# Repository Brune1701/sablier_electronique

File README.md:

# sablier_electronique

## Présentation

J'ai choisi de construire un minuteur, sablier, qui lance un compte à rebours de 60 sec. 
Le système s'actualise et recommence lorsqu'il est tourné, tel un sablier mécanique.

## Fonctionnement et Composants : 

- Détection de l'orientation avec le LIS3DH
- Microcontrôleur ATmega328P-AU
- 12 LEDs  pour représenter le sable qui s'écoule
- Compte à rebours de 60 secondes
- Buzzer en fin de minuterie
- Batterie rechargeable par USB-C

## Schéma électronique

## PCB

## Vue 3D

## Tests

Le PCB devra être soudé puis testé afin de vérifier :
- la détection de l'orientation ;
- le fonctionnement des LEDs ;
- le décompte de 60 secondes ;
- le fonctionnement du buzzer ;
- la recharge de la batterie.

Je n'ai pas pu achever le traçage des pistes malgré les explications d'un professeur du fablab. Ainsi, il me reste des erreurs d'isolations principalement :)

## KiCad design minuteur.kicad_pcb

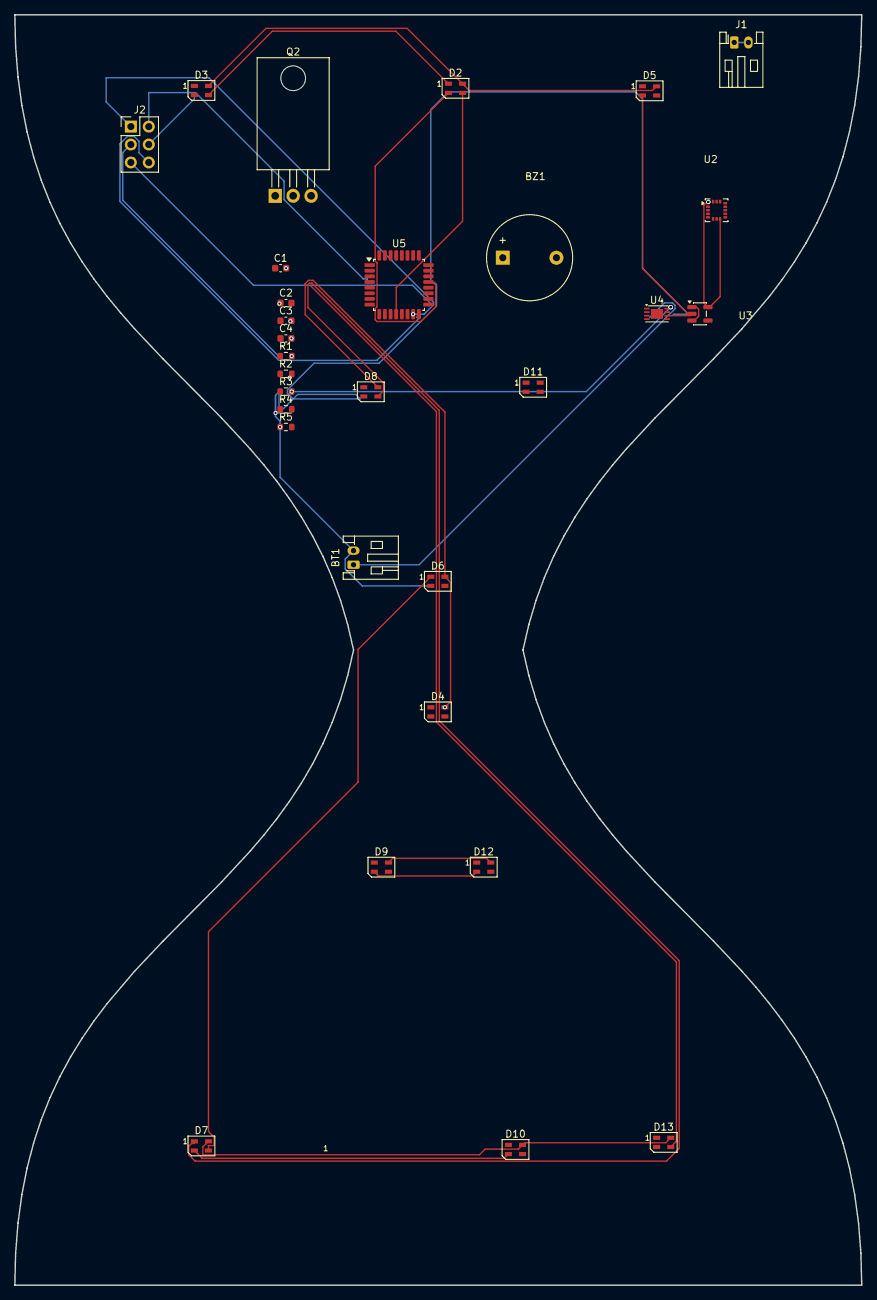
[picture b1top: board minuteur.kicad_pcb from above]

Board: 2 copper layers, 120.0 x 180.0 mm, 30 parts (0 on the bottom side), 32 nets.

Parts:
BT1: Battery_Cell; JST_PH_S2B-PH-K_1x02_P2.00mm_Horizontal
BZ1: Buzzer; Buzzer_12x9.5RM7.6
C1: 100 nF; C_0603_1608Metric
C2, C3, C4: C; C_0603_1608Metric
D2, D3, D4, D5, D6, D7, D8, D9, D10, D11, D12, D13: SK6805; LED_SK6805_PLCC4_2.4x2.7mm_P1.3mm
J1: USB_C_Receptacle_USB2.0_16P; JST_PH_S2B-PH-K_1x02_P2.00mm_Horizontal
J2: Conn_02x03_Odd_Even; PinHeader_2x03_P2.54mm_Vertical
Q2: IRLB8721; TO-220-3_Horizontal_TabDown
R1: 10000; R_0603_1608Metric
R2: 1000; R_0603_1608Metric
R3: 2 000; R_0603_1608Metric
R4: 5100; R_0603_1608Metric
R5: R; R_0603_1608Metric
U2: LIS3DH; LGA-16_3x3mm_P0.5mm_LayoutBorder3x5y
U3: AP2112K-3.3; SOT-23-5
U4: MCP73831-2-MC; DFN-8-1EP_3x2mm_P0.5mm_EP1.7x1.4mm
U5: ATmega328P-A; TQFP-32_7x7mm_P0.8mm

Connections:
+3.3V: BZ1.1 (+), J2.2, U2.1 (VDD_IO), U2.8 (CS), U2.14 (VDD), U3.5 (VOUT), U5.4 (VCC), U5.6 (VCC), U5.18 (AVCC)
+5V: U4.1 (V_{DD}), U4.2 (V_{DD})
/BAT +: BT1.1 (+), U4.3 (V_{BAT}), U4.4 (V_{BAT})
/BAT +_inter: D2.4 (VDD), D3.4 (VDD), D4.4 (VDD), D5.4 (VDD), D6.4 (VDD), D7.4 (VDD), D8.4 (VDD), D9.4 (VDD), D10.4 (VDD), D11.4 (VDD), D12.4 (VDD), D13.4 (VDD), U3.1 (VIN), U3.3 (EN)
/MISO: J2.6, U5.16 (PB4)
/MOSI: J2.1, U5.15 (PB3)
/RESET: J2.3, R1.1
/SCK: J2.5, U5.17 (PB5)
GND: BT1.2 (-), C1.1, D2.2 (VSS), D3.2 (VSS), D4.2 (VSS), D5.2 (VSS), D6.2 (VSS), D7.2 (VSS), D8.2 (VSS), D9.2 (VSS), D10.2 (VSS), D11.2 (VSS), D12.2 (VSS), D13.2 (VSS), J2.4, Q2.1 (S), R3.1, R4.1, R5.1, U2.5 (GND), U2.7 (SDO), U2.10 (GND), U2.12 (GND), U3.2 (GND), U4.6 (V_{SS}), U5.3 (GND), U5.5 (GND), U5.21 (GND)
unnamed: BZ1.2 (-), Q2.3 (D)
unnamed: D2.3 (DIN), U5.12 (PB0)
unnamed: D2.1 (DOUT), D3.3 (DIN)
unnamed: C4.1, D3.1 (DOUT)
unnamed: C4.2, D4.3 (DIN)
unnamed: D4.1 (DOUT), D5.3 (DIN)
unnamed: D5.1 (DOUT), D6.3 (DIN)
unnamed: D6.1 (DOUT), D7.3 (DIN)
unnamed: D7.1 (DOUT), D8.3 (DIN)
unnamed: D8.1 (DOUT), D9.3 (DIN)
unnamed: D9.1 (DOUT), D10.3 (DIN)
unnamed: C3.1, D10.1 (DOUT)
unnamed: C3.2, D11.3 (DIN)
unnamed: D11.1 (DOUT), D12.3 (DIN)
unnamed: C2.1, D12.1 (DOUT)
unnamed: C2.2, D13.3 (DIN)
unnamed: Q2.2 (G), R2.1
unnamed: U2.6 (SDI), U5.27 (PC4)
unnamed: U2.4 (SPC), U5.28 (PC5)
unnamed: R3.2, U4.8 (PROG)
unnamed: C1.2, U5.20 (AREF)
unnamed: R2.2, U5.13 (PB1)
unnamed: R1.2, U5.29 (~RESET/PC6)
